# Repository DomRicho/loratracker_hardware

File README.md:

# LoRa Tracker HAT+

This board was developed for my engineering honours project, exploring how LoRa—a low-power, long-range wireless technology—could improve animal tracking. 
Now LoRa is already well established in this field. However, is removing the need for GNSS by localising using the LoRa packets possible? 
This could simplify devices, save battery, and reduce interference with wildlife behaviour, especially for small or sensitive species 
like wild bilbies.

The project investigates two localisation methods: **RSSI** and **Time-Difference of Arrival (TDoA)**.

The HAT+ is a custom Raspberry Pi board featuring an STM32H7, GNSS module, LoRa modem, and I2C environmental sensor. 
Three boards act as anchors to trilaterate LoRa packet sources. To handle packets moving at the speed of light, the
anchors are synchronised via GPS pulse-per-second signals, keeping jitter under 20 ns.

## Issues

- CADDetected on the SX1272 couldn’t reliably timestamp preambles; switched to using the **ValidHeader** flag instead.  
- DIO4 trace was cut, and DIO3 was rerouted to the STM32H7 input capture pin.  
- Standard crystals drift roughly 20 µs, translating to tens of km of error. Achieving nanosecond-level timing 
requires expensive oven-controlled crystals (~$450 for three), compared to ~$0.60 for standard ones. Lesson learned

## Future Plans
- Battery power  
- Solar charging

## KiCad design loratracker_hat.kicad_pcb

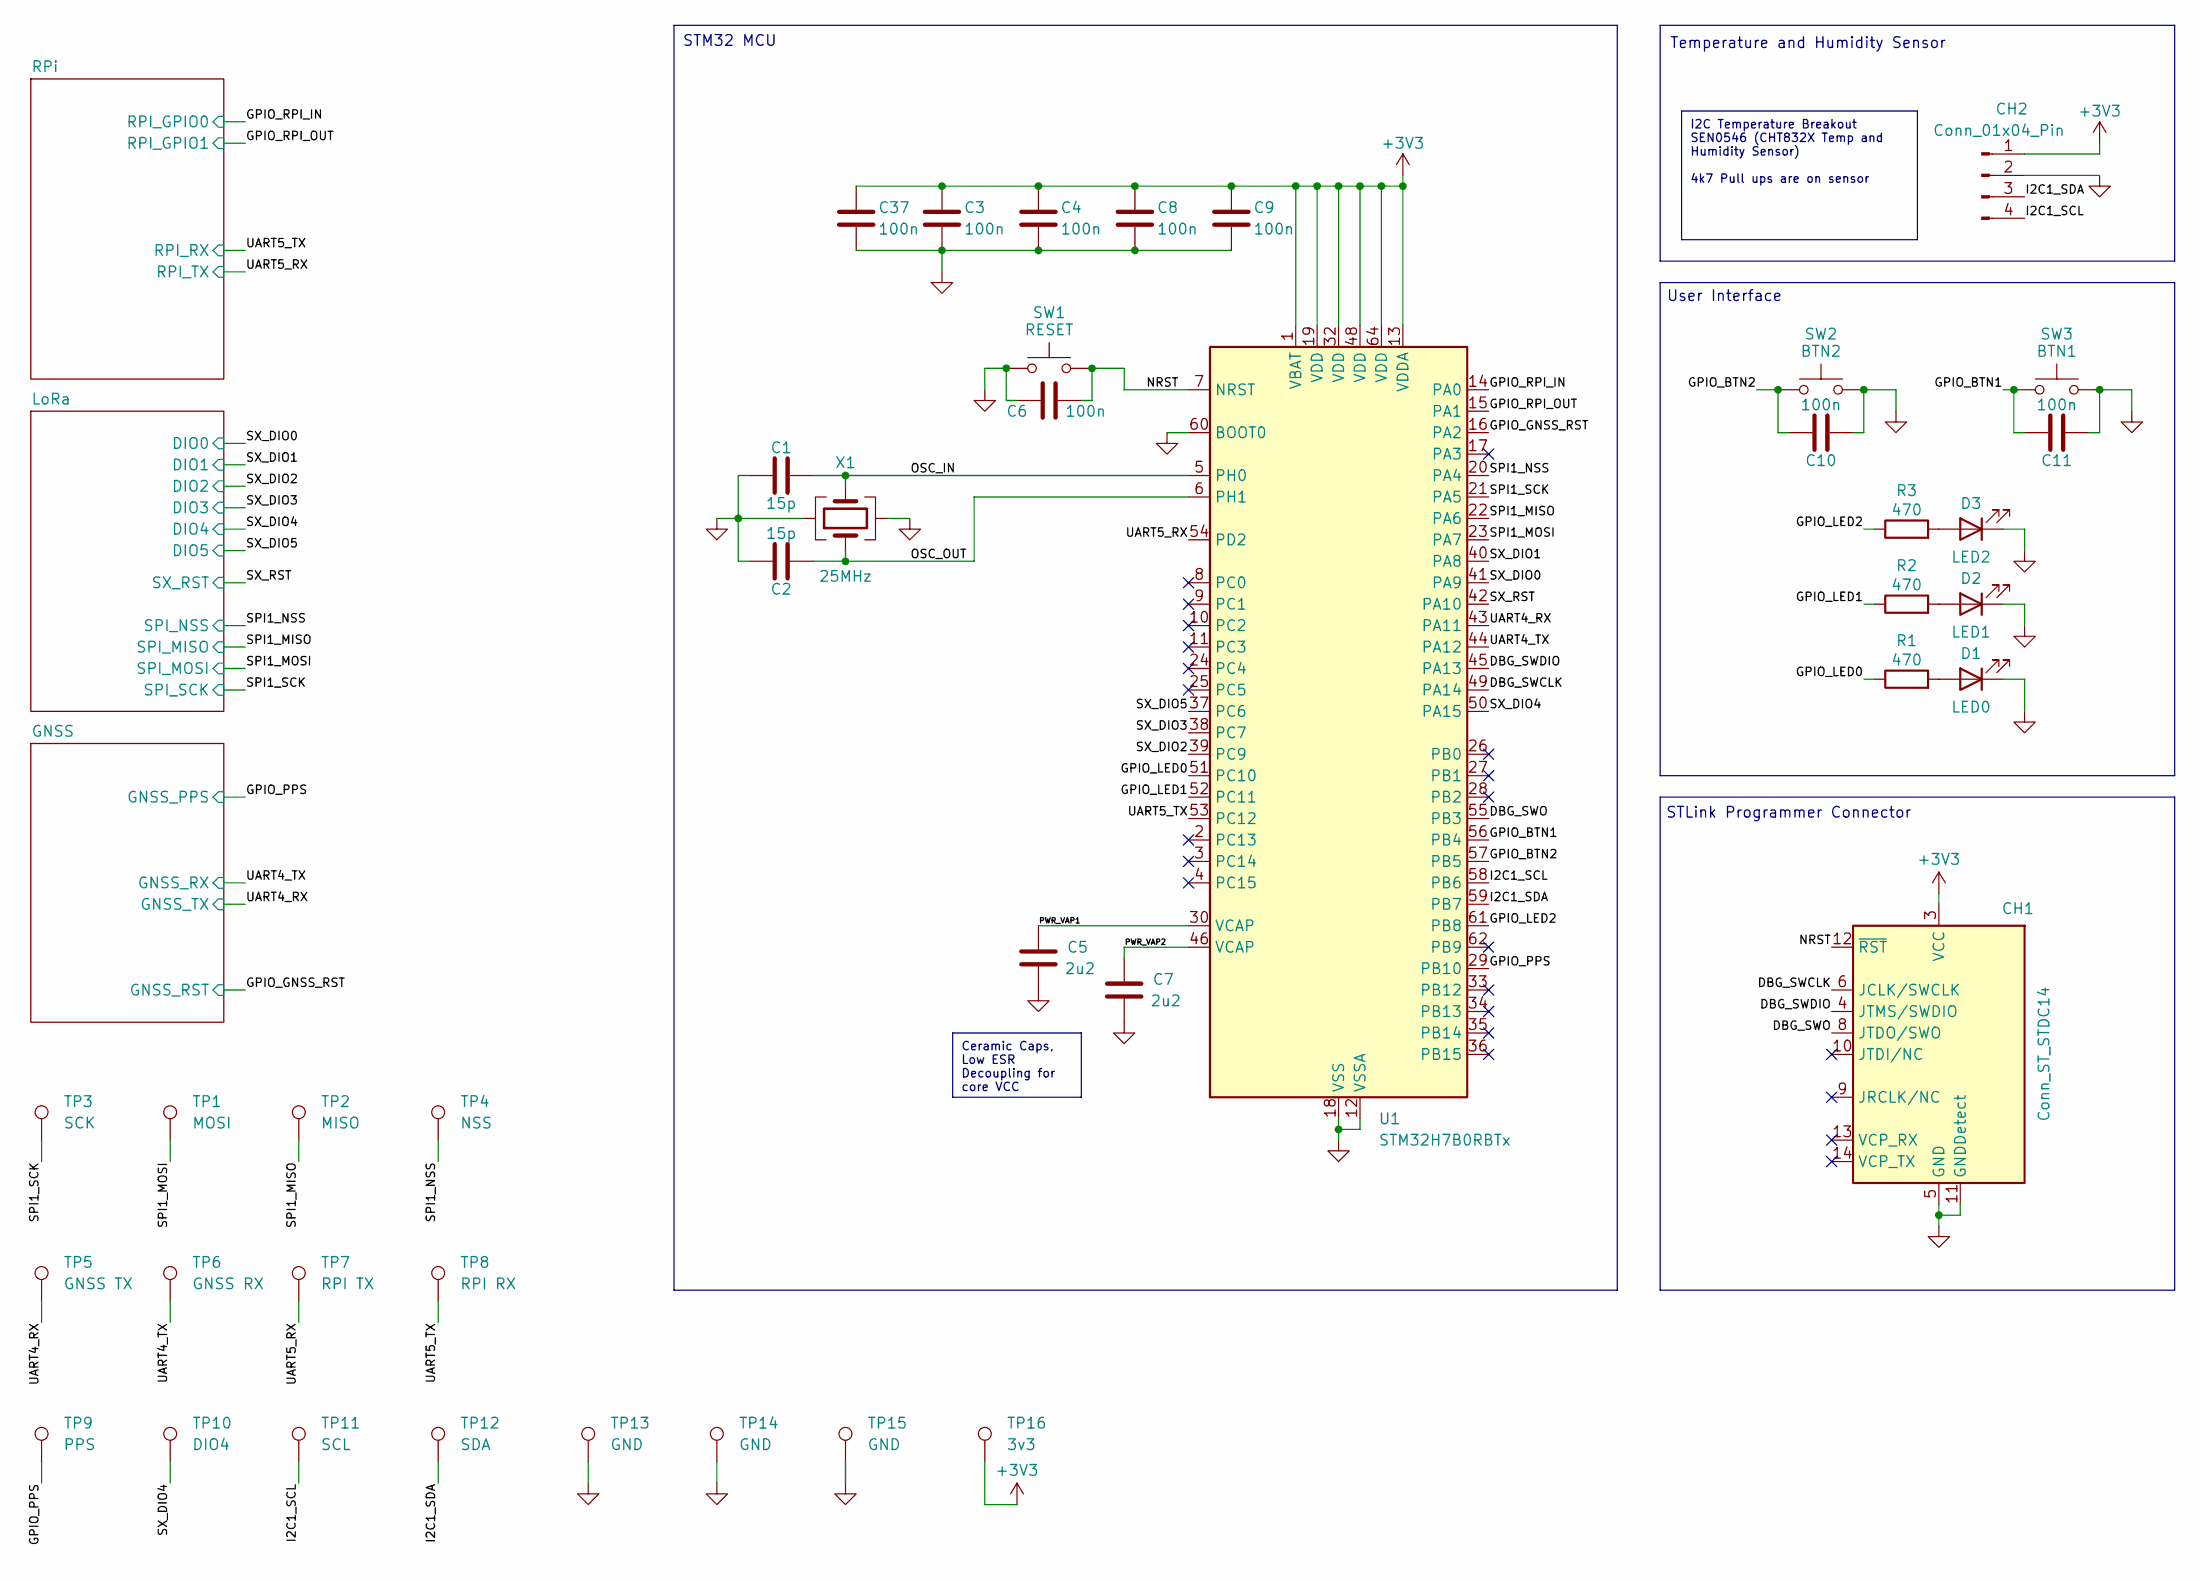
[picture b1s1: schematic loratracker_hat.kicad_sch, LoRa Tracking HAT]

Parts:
C1, C2: 15p; C_0402_1005Metric
C3, C4, C6, C8, C9, C10, C11, C37: 100n; C_0402_1005Metric
C5, C7: 2u2; C_0603_1608Metric
CH1: Conn_ST_STDC14; SAMTEC_FTSH-107-01-L-DV-A-TR
CH2: Conn_01x04_Pin; PinHeader_1x04_P2.54mm_Vertical
D1: LED0; LED_0402_1005Metric
D2: LED1; LED_0402_1005Metric
D3: LED2; LED_0402_1005Metric
R1, R2, R3: 470; R_0402_1005Metric
SW1: RESET; PTS636SM43SMTR
SW2: BTN2; PTS636SM43SMTR
SW3: BTN1; PTS636SM43SMTR
TP1: MOSI; TestPoint_Pad_1.0x1.0mm
TP2: MISO; TestPoint_Pad_1.0x1.0mm
TP3: SCK; TestPoint_Pad_1.0x1.0mm
TP4: NSS; TestPoint_Pad_1.0x1.0mm
TP5: GNSS TX; TestPoint_Pad_1.0x1.0mm
TP6: GNSS RX; TestPoint_Pad_1.0x1.0mm
TP7: RPI TX; TestPoint_Pad_1.0x1.0mm
TP8: RPI RX; TestPoint_Pad_1.0x1.0mm
TP9: PPS; TestPoint_Pad_1.0x1.0mm
TP10: DIO4; TestPoint_Pad_1.0x1.0mm
TP11: SCL; TestPoint_Pad_1.0x1.0mm
TP12: SDA; TestPoint_Pad_1.0x1.0mm
TP13, TP14, TP15: GND; TestPoint_Pad_1.0x1.0mm
TP16: 3v3; TestPoint_Pad_1.0x1.0mm
U1: STM32H7B0RBTx; LQFP-64_10x10mm_P0.5mm
X1: 25MHz; Crystal_SMD_2016-4Pin_2.0x1.6mm

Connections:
+3V3: C3.1, C4.1, C8.1, C9.1, C37.1, CH1.3 (VCC), CH2.1, TP16.1, U1.1 (VBAT), U1.13 (VDDA), U1.19 (VDD), U1.32 (VDD), U1.48 (VDD), U1.64 (VDD); also elsewhere on the board
/DBG_SWCLK: CH1.6 (JCLK/SWCLK), U1.49 (PA14)
/DBG_SWDIO: CH1.4 (JTMS/SWDIO), U1.45 (PA13)
/DBG_SWO: CH1.8 (JTDO/SWO), U1.55 (PB3)
/GPIO_BTN1: C11.2, SW3.1, U1.56 (PB4)
/GPIO_BTN2: C10.2, SW2.1, U1.57 (PB5)
/GPIO_GNSS_RST: U1.16 (PA2); also elsewhere on the board
/GPIO_LED0: R1.1, U1.51 (PC10)
/GPIO_LED1: R2.1, U1.52 (PC11)
/GPIO_LED2: R3.1, U1.61 (PB8)
/GPIO_PPS: TP9.1, U1.29 (PB10); also elsewhere on the board
/GPIO_RPI_IN: U1.14 (PA0); also elsewhere on the board
/GPIO_RPI_OUT: U1.15 (PA1); also elsewhere on the board
/I2C1_SCL: CH2.4, TP11.1, U1.58 (PB6)
/I2C1_SDA: CH2.3, TP12.1, U1.59 (PB7)
/NRST: C6.1, CH1.12 (~RST), SW1.2, U1.7 (NRST)
/OSC_IN: C1.2, U1.5 (PH0), X1.3
/OSC_OUT: C2.1, U1.6 (PH1), X1.1
/PWR_VAP1: C5.1, U1.30 (VCAP)
/PWR_VAP2: C7.1, U1.46 (VCAP)
/SPI1_MISO: TP2.1, U1.22 (PA6); also elsewhere on the board
/SPI1_MOSI: TP1.1, U1.23 (PA7); also elsewhere on the board
/SPI1_NSS: TP4.1, U1.20 (PA4); also elsewhere on the board
/SPI1_SCK: TP3.1, U1.21 (PA5); also elsewhere on the board
/SX_DIO0: U1.41 (PA9); also elsewhere on the board
/SX_DIO1: U1.40 (PA8); also elsewhere on the board
/SX_DIO2: U1.39 (PC9); also elsewhere on the board
/SX_DIO3: U1.38 (PC7); also elsewhere on the board
/SX_DIO4: TP10.1, U1.50 (PA15); also elsewhere on the board
/SX_DIO5: U1.37 (PC6); also elsewhere on the board
/SX_RST: U1.42 (PA10); also elsewhere on the board
/UART4_RX: TP5.1, U1.43 (PA11); also elsewhere on the board
/UART4_TX: TP6.1, U1.44 (PA12); also elsewhere on the board
/UART5_RX: TP7.1, U1.54 (PD2); also elsewhere on the board
/UART5_TX: TP8.1, U1.53 (PC12); also elsewhere on the board
GND: C1.1, C2.2, C3.2, C4.2, C5.2, C6.2, C7.2, C8.2, C9.2, C10.1, C11.1, C37.2, CH1.5 (GND), CH1.7 (GND), CH1.11 (GNDDetect), CH2.2, D1.1 (K), D2.1 (K), D3.1 (K), SW1.1, SW2.2, SW3.2, TP13.1, TP14.1, TP15.1, U1.12 (VSSA), U1.18 (VSS), U1.31 (VSS), U1.47 (VSS), U1.60 (BOOT0), U1.63 (VSS), X1.2, X1.4; also elsewhere on the board
unnamed: D1.2 (A), R1.2
unnamed: D2.2 (A), R2.2
unnamed: D3.2 (A), R3.2

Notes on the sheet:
STLink Programmer Connector
Temperature and Humidity Sensor
STM32 MCU
User Interface
I2C Temperature Breakout SEN0546 (CHT832X Temp and Humidity Sensor) 4k7 Pull ups are on sensor
Ceramic Caps, Low ESR Decoupling for core VCC

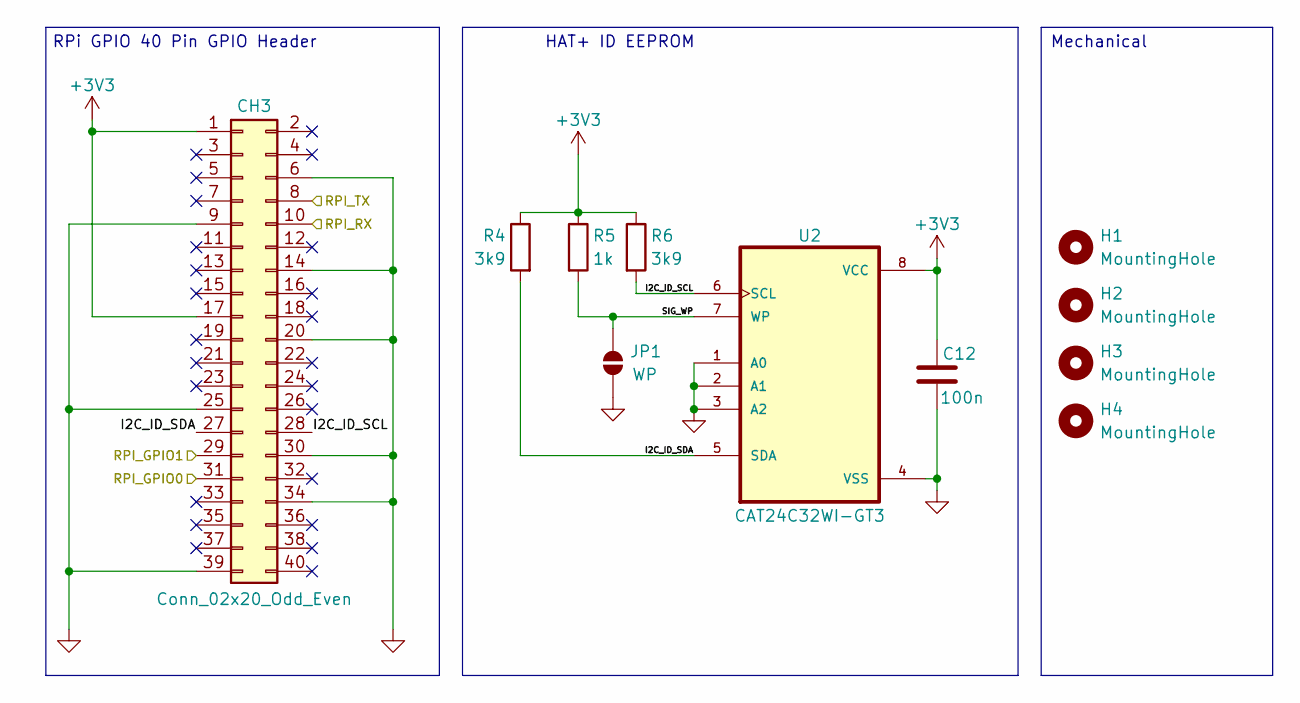
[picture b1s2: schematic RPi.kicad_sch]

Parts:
C12: 100n; C_0402_1005Metric
CH3: Conn_02x20_Odd_Even; PinHeader_2x20_P2.54mm_Vertical
H1, H2, H3, H4: MountingHole; RPi_mounting_holes
JP1: WP; R_0805_2012Metric
R4, R6: 3k9; R_0402_1005Metric
R5: 1k; R_0402_1005Metric
U2: CAT24C32WI-GT3; SOIC127P600X175-8N

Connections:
+3V3: C12.1, CH3.1, CH3.17, R4.1, R5.1, R6.1, U2.8 (VCC); also elsewhere on the board
/GPIO_RPI_IN: CH3.31; also elsewhere on the board
/GPIO_RPI_OUT: CH3.29; also elsewhere on the board
/RPi/I2C_ID_SCL: CH3.28, R6.2, U2.6 (SCL)
/RPi/I2C_ID_SDA: CH3.27, R4.2, U2.5 (SDA)
/RPi/SIG_WP: JP1.2 (B), R5.2, U2.7 (WP)
/UART5_RX: CH3.8; also elsewhere on the board
/UART5_TX: CH3.10; also elsewhere on the board
GND: C12.2, CH3.6, CH3.9, CH3.14, CH3.20, CH3.25, CH3.30, CH3.34, CH3.39, JP1.1 (A), U2.1 (A0), U2.2 (A1), U2.3 (A2), U2.4 (VSS); also elsewhere on the board

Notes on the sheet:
RPi GPIO 40 Pin GPIO Header
HAT+ ID EEPROM
Mechanical

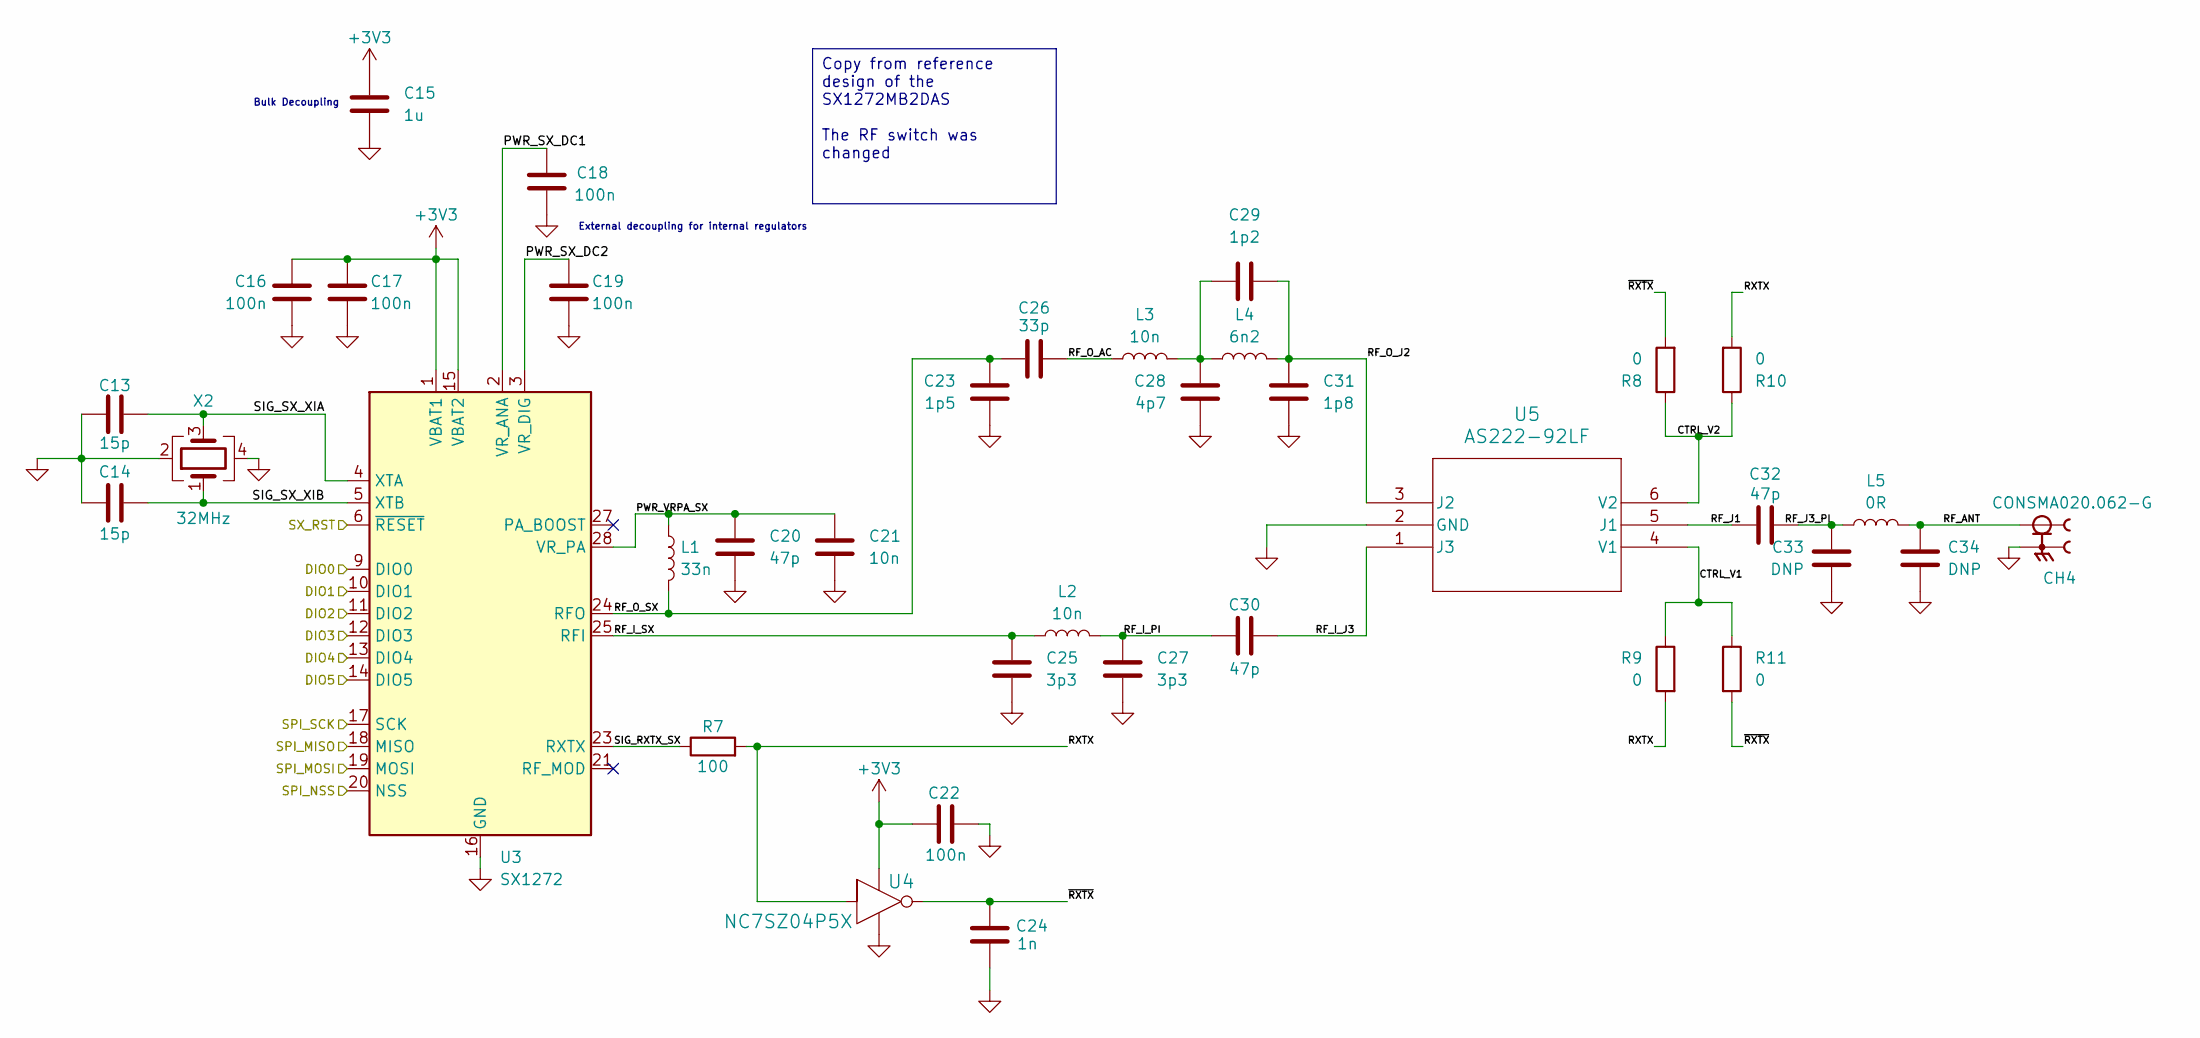
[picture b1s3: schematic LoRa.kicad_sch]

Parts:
C13, C14: 15p; C_0402_1005Metric
C15: 1u; C_0402_1005Metric
C16, C17, C18, C19, C22: 100n; C_0402_1005Metric
C20, C30, C32: 47p; C_0402_1005Metric
C21: 10n; C_0402_1005Metric
C23: 1p5; C_0402_1005Metric
C24: 1n; C_0402_1005Metric
C25, C27: 3p3; C_0402_1005Metric
C26: 33p; C_0402_1005Metric
C28: 4p7; C_0402_1005Metric
C29: 1p2; C_0402_1005Metric
C31: 1p8; C_0402_1005Metric
C33, C34: DNP; C_0402_1005Metric
CH4: CONSMA020.062-G; LINX_CONSMA020.062-G
L1: 33n; L_0402_1005Metric
L2, L3: 10n; L_0402_1005Metric
L4: 6n2; L_0402_1005Metric
L5: 0R; L_0402_1005Metric
R7: 100; R_0402_1005Metric
R8, R9, R10, R11: 0; R_0402_1005Metric
U3: SX1272; QFN-28-1EP_6x6mm_P0.65mm_EP4.8x4.8mm
U4: NC7SZ04P5X; SC-88A-5_1P35X2P2_ONS
U5: AS222-92LF; SC-70-6_PSM
X2: 32MHz; Crystal_SMD_2016-4Pin_2.0x1.6mm

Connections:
+3V3: C15.1, C16.1, C17.1, C22.1, U3.1 (VBAT1), U3.15 (VBAT2), U4.5; also elsewhere on the board
/LoRa/CTRL_V1: R9.1, R11.1, U5.4 (V1)
/LoRa/CTRL_V2: R8.1, R10.1, U5.6 (V2)
/LoRa/PWR_SX_DC1: C18.1, U3.2 (VR_ANA)
/LoRa/PWR_SX_DC2: C19.1, U3.3 (VR_DIG)
/LoRa/PWR_VRPA_SX: C20.1, C21.1, L1.1, U3.28 (VR_PA)
/LoRa/RF_ANT: C34.2, CH4.1, L5.2
/LoRa/RF_I_J3: C30.2, U5.1 (J3)
/LoRa/RF_I_PI: C27.1, C30.1, L2.2
/LoRa/RF_I_SX: C25.1, L2.1, U3.25 (RFI)
/LoRa/RF_J1: C32.1, U5.5 (J1)
/LoRa/RF_J3_PI: C32.2, C33.2, L5.1
/LoRa/RF_O_AC: C26.2, L3.1
/LoRa/RF_O_J2: C29.2, C31.2, L4.2, U5.3 (J2)
/LoRa/RF_O_SX: C23.1, C26.1, L1.2, U3.24 (RFO)
/LoRa/RXTX: R7.2, R9.2, R10.2, U4.2
/LoRa/SIG_RXTX_SX: R7.1, U3.23 (RXTX)
/LoRa/SIG_SX_XIA: C13.1, U3.4 (XTA), X2.3
/LoRa/SIG_SX_XIB: C14.1, U3.5 (XTB), X2.1
/LoRa/~RXTX: C24.1, R8.2, R11.2, U4.4
/SPI1_MISO: U3.18 (MISO); also elsewhere on the board
/SPI1_MOSI: U3.19 (MOSI); also elsewhere on the board
/SPI1_NSS: U3.20 (NSS); also elsewhere on the board
/SPI1_SCK: U3.17 (SCK); also elsewhere on the board
/SX_DIO0: U3.9 (DIO0); also elsewhere on the board
/SX_DIO1: U3.10 (DIO1); also elsewhere on the board
/SX_DIO2: U3.11 (DIO2); also elsewhere on the board
/SX_DIO3: U3.12 (DIO3); also elsewhere on the board
/SX_DIO4: U3.13 (DIO4); also elsewhere on the board
/SX_DIO5: U3.14 (DIO5); also elsewhere on the board
/SX_RST: U3.6 (~RESET); also elsewhere on the board
GND: C13.2, C14.2, C15.2, C16.2, C17.2, C18.2, C19.2, C20.2, C21.2, C22.2, C23.2, C24.2, C25.2, C27.2, C28.1, C31.1, C33.1, C34.1, CH4.S1, CH4.S2, CH4.S3, CH4.S4, U3.16 (GND), U3.22 (GND), U3.26 (GND), U3.29 (GND), U4.3, U5.2 (GND), X2.2, X2.4; also elsewhere on the board
unnamed: C28.2, C29.1, L3.2, L4.1

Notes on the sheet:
Bulk Decoupling
External decoupling for internal regulators
Copy from reference design of the SX1272MB2DAS The RF switch was changed

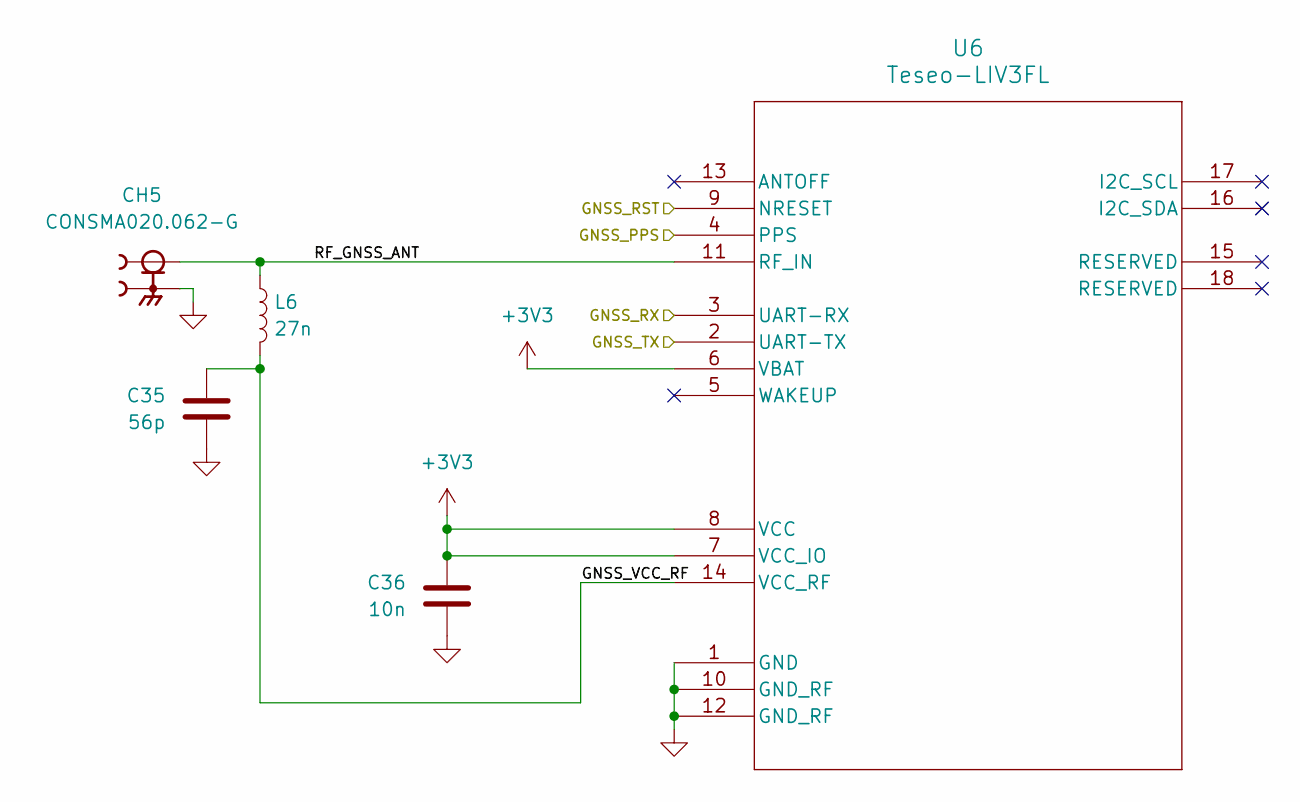
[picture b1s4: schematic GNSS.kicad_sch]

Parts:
C35: 56p; C_0402_1005Metric
C36: 10n; C_0402_1005Metric
CH5: CONSMA020.062-G; LINX_CONSMA020.062-G
L6: 27n; L_0402_1005Metric
U6: Teseo-LIV3FL; LIV3FL_STM

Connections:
+3V3: C36.1, U6.6 (VBAT), U6.7 (VCC_IO), U6.8 (VCC); also elsewhere on the board
/GNSS/GNSS_VCC_RF: C35.1, L6.2, U6.14 (VCC_RF)
/GNSS/RF_GNSS_ANT: CH5.1, L6.1, U6.11 (RF_IN)
/GPIO_GNSS_RST: U6.9 (NRESET); also elsewhere on the board
/GPIO_PPS: U6.4 (PPS); also elsewhere on the board
/UART4_RX: U6.2 (UART-TX); also elsewhere on the board
/UART4_TX: U6.3 (UART-RX); also elsewhere on the board
GND: C35.2, C36.2, CH5.S1, CH5.S2, CH5.S3, CH5.S4, U6.1 (GND), U6.10 (GND_RF), U6.12 (GND_RF); also elsewhere on the board

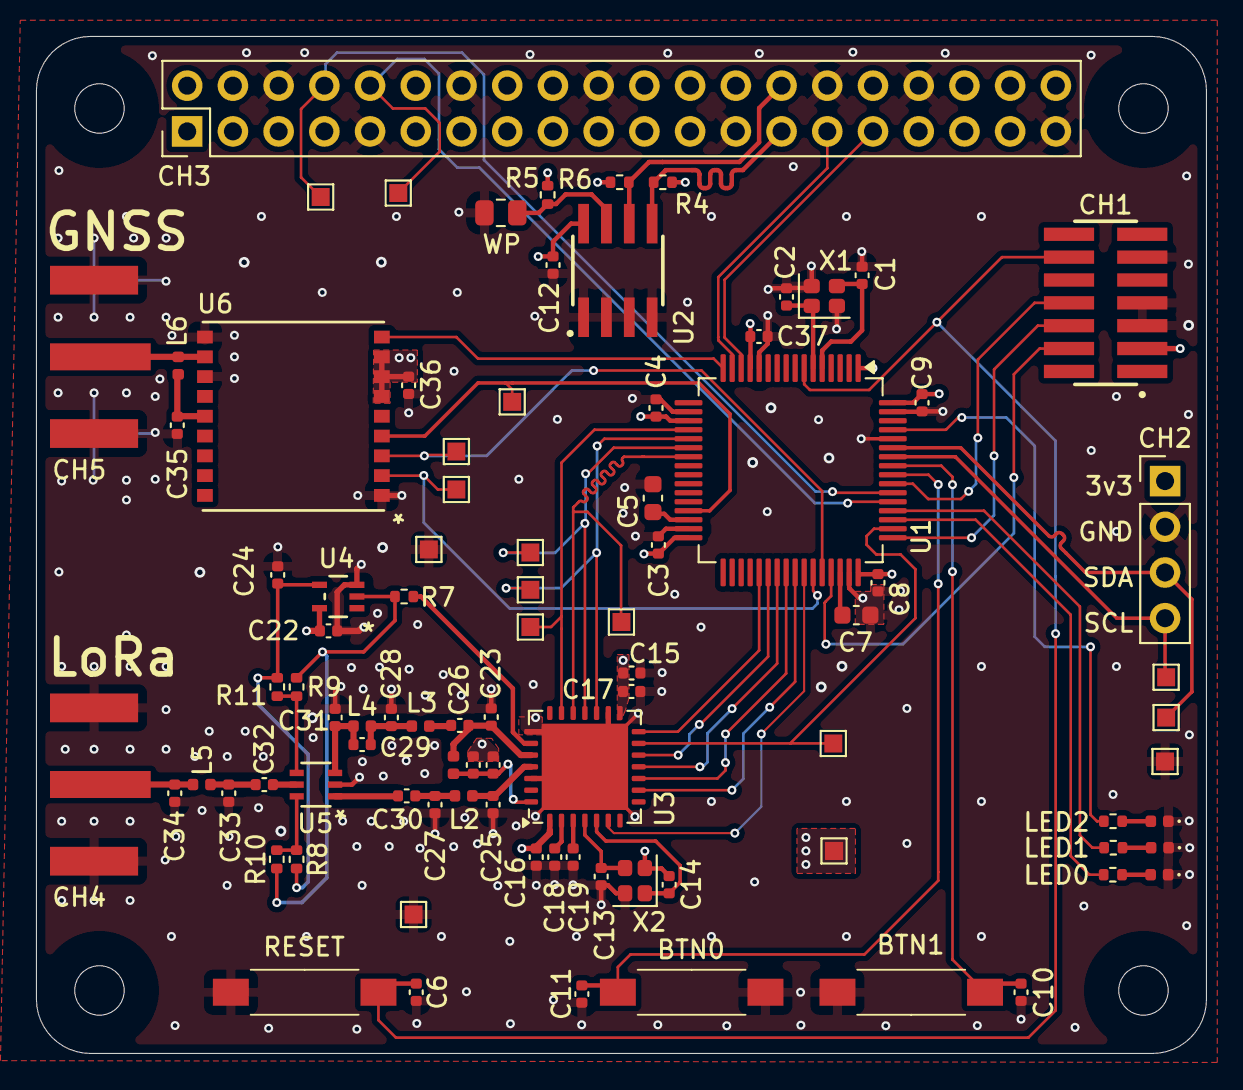
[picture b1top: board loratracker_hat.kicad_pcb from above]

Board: 4 copper layers, 65.0 x 56.5 mm, 94 parts (0 on the bottom side), 64 nets.

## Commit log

2025-09-02 LoRa Tracker HAT+ v1.0
2025-09-02 add readme
2025-09-02 remove space from folder
2025-09-02 add combined pdf for layout
2025-09-02 update issues and readme
2025-09-02 fix image
